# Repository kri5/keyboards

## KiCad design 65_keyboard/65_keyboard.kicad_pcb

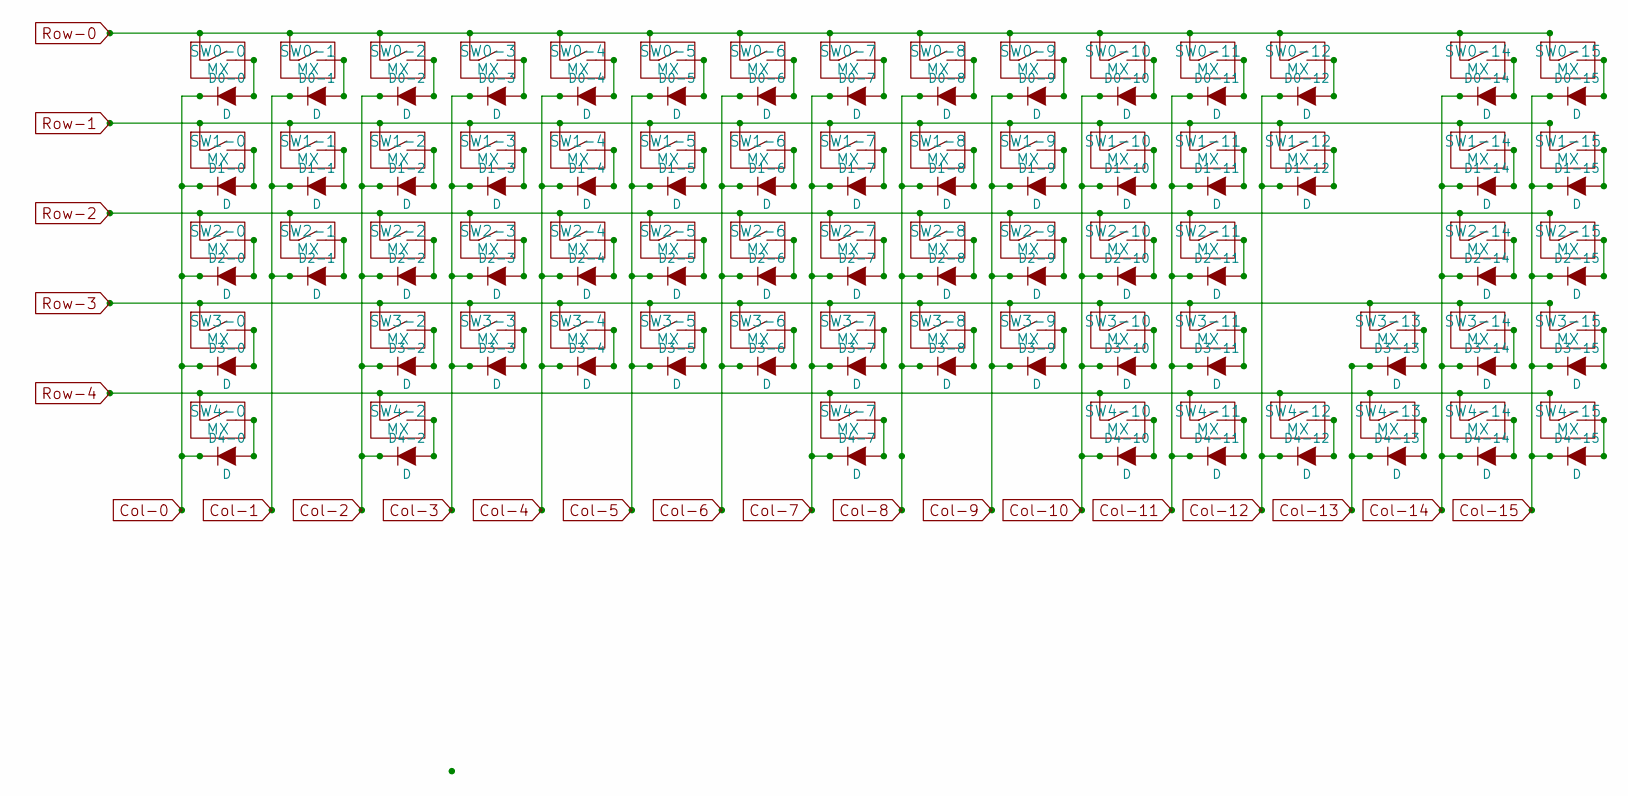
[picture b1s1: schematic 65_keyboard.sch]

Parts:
D0-0, D0-1, D0-2, D0-3, D0-4, D0-5, D0-6, D0-7, D0-8, D0-9, D0-10, D0-11, D0-12, D0-14, D0-15, D1-0, D1-1, D1-2, D1-3, D1-4, D1-5, D1-6, D1-7, D1-8, D1-9, D1-10, D1-11, D1-12, D1-14, D1-15, D2-0, D2-1, D2-2, D2-3, D2-4, D2-5, D2-6, D2-7, D2-8, D2-9, D2-10, D2-11, D2-14, D2-15, D3-0, D3-2, D3-3, D3-4, D3-5, D3-6, D3-7, D3-8, D3-9, D3-10, D3-11, D3-13, D3-14, D3-15, D4-0, D4-2, D4-7, D4-10, D4-11, D4-12, D4-13, D4-14, D4-15: D; Diode_DO-35_SOD27_Horizontal_RM10
SW0-0, SW0-1, SW0-2, SW0-3, SW0-4, SW0-5, SW0-6, SW0-7, SW0-8, SW0-9, SW0-10, SW0-11, SW0-12, SW0-15, SW1-1, SW1-2, SW1-3, SW1-4, SW1-5, SW1-6, SW1-7, SW1-8, SW1-9, SW1-10, SW1-11, SW1-12, SW1-15, SW2-1, SW2-2, SW2-3, SW2-4, SW2-5, SW2-6, SW2-7, SW2-8, SW2-9, SW2-10, SW2-11, SW2-15, SW3-2, SW3-3, SW3-4, SW3-5, SW3-6, SW3-7, SW3-8, SW3-9, SW3-10, SW3-11, SW3-14, SW3-15, SW4-11, SW4-13, SW4-14, SW4-15: MX; CHERRY_PLATE_100H
SW0-14: MX; CHERRY_PLATE_200H
SW1-0, SW1-14, SW4-2: MX; CHERRY_PLATE_150H
SW2-0, SW3-13, SW4-0: MX; CHERRY_PLATE_175H
SW2-14, SW3-0: MX; CHERRY_PLATE_225H
SW4-7: MX; CHERRY_PLATE_625H
SW4-10, SW4-12: MX; CHERRY_PLATE_125H

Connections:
Col-0: D0-0.1 (K), D1-0.1 (K), D2-0.1 (K), D3-0.1 (K), D4-0.1 (K)
Col-1: D0-1.1 (K), D1-1.1 (K), D2-1.1 (K)
Col-2: D0-2.1 (K), D1-2.1 (K), D2-2.1 (K), D3-2.1 (K), D4-2.1 (K)
Col-3: D0-3.1 (K), D1-3.1 (K), D2-3.1 (K), D3-3.1 (K)
Col-4: D0-4.1 (K), D1-4.1 (K), D2-4.1 (K), D3-4.1 (K)
Col-5: D0-5.1 (K), D1-5.1 (K), D2-5.1 (K), D3-5.1 (K)
Col-6: D0-6.1 (K), D1-6.1 (K), D2-6.1 (K), D3-6.1 (K)
Col-7: D0-7.1 (K), D1-7.1 (K), D2-7.1 (K), D3-7.1 (K), D4-7.1 (K)
Col-8: D0-8.1 (K), D1-8.1 (K), D2-8.1 (K), D3-8.1 (K)
Col-9: D0-9.1 (K), D1-9.1 (K), D2-9.1 (K), D3-9.1 (K)
Col-10: D0-10.1 (K), D1-10.1 (K), D2-10.1 (K), D3-10.1 (K), D4-10.1 (K)
Col-11: D0-11.1 (K), D1-11.1 (K), D2-11.1 (K), D3-11.1 (K), D4-11.1 (K)
Col-12: D0-12.1 (K), D1-12.1 (K), D4-12.1 (K)
Col-13: D3-13.1 (K), D4-13.1 (K)
Col-14: D0-14.1 (K), D1-14.1 (K), D2-14.1 (K), D3-14.1 (K), D4-14.1 (K)
Col-15: D0-15.1 (K), D1-15.1 (K), D2-15.1 (K), D3-15.1 (K), D4-15.1 (K)
unnamed: D0-0.2 (A), SW0-0.2 (B)
unnamed: D0-1.2 (A), SW0-1.2 (B)
unnamed: D0-2.2 (A), SW0-2.2 (B)
unnamed: D0-3.2 (A), SW0-3.2 (B)
unnamed: D0-4.2 (A), SW0-4.2 (B)
unnamed: D0-5.2 (A), SW0-5.2 (B)
unnamed: D0-6.2 (A), SW0-6.2 (B)
unnamed: D0-7.2 (A), SW0-7.2 (B)
unnamed: D0-8.2 (A), SW0-8.2 (B)
unnamed: D0-9.2 (A), SW0-9.2 (B)
unnamed: D0-10.2 (A), SW0-10.2 (B)
unnamed: D0-11.2 (A), SW0-11.2 (B)
unnamed: D0-12.2 (A), SW0-12.2 (B)
unnamed: D0-14.2 (A), SW0-14.2 (B)
unnamed: D0-15.2 (A), SW0-15.2 (B)
unnamed: D1-0.2 (A), SW1-0.2 (B)
unnamed: D1-1.2 (A), SW1-1.2 (B)
unnamed: D1-2.2 (A), SW1-2.2 (B)
unnamed: D1-3.2 (A), SW1-3.2 (B)
unnamed: D1-4.2 (A), SW1-4.2 (B)
unnamed: D1-5.2 (A), SW1-5.2 (B)
unnamed: D1-6.2 (A), SW1-6.2 (B)
unnamed: D1-7.2 (A), SW1-7.2 (B)
unnamed: D1-8.2 (A), SW1-8.2 (B)
unnamed: D1-9.2 (A), SW1-9.2 (B)
unnamed: D1-10.2 (A), SW1-10.2 (B)
unnamed: D1-11.2 (A), SW1-11.2 (B)
unnamed: D1-12.2 (A), SW1-12.2 (B)
unnamed: D1-14.2 (A), SW1-14.2 (B)
unnamed: D1-15.2 (A), SW1-15.2 (B)
unnamed: D2-0.2 (A), SW2-0.2 (B)
unnamed: D2-1.2 (A), SW2-1.2 (B)
unnamed: D2-2.2 (A), SW2-2.2 (B)
unnamed: D2-3.2 (A), SW2-3.2 (B)
unnamed: D2-4.2 (A), SW2-4.2 (B)
unnamed: D2-5.2 (A), SW2-5.2 (B)
unnamed: D2-6.2 (A), SW2-6.2 (B)
unnamed: D2-7.2 (A), SW2-7.2 (B)
unnamed: D2-8.2 (A), SW2-8.2 (B)
unnamed: D2-9.2 (A), SW2-9.2 (B)
unnamed: D2-10.2 (A), SW2-10.2 (B)
unnamed: D2-11.2 (A), SW2-11.2 (B)
unnamed: D2-14.2 (A), SW2-14.2 (B)
unnamed: D2-15.2 (A), SW2-15.2 (B)
unnamed: D3-0.2 (A), SW3-0.2 (B)
unnamed: D3-2.2 (A), SW3-2.2 (B)
unnamed: D3-3.2 (A), SW3-3.2 (B)
unnamed: D3-4.2 (A), SW3-4.2 (B)
unnamed: D3-5.2 (A), SW3-5.2 (B)
unnamed: D3-6.2 (A), SW3-6.2 (B)
unnamed: D3-7.2 (A), SW3-7.2 (B)
unnamed: D3-8.2 (A), SW3-8.2 (B)
unnamed: D3-9.2 (A), SW3-9.2 (B)
unnamed: D3-10.2 (A), SW3-10.2 (B)
unnamed: D3-11.2 (A), SW3-11.2 (B)
unnamed: D3-13.2 (A), SW3-13.2 (B)
unnamed: D3-14.2 (A), SW3-14.2 (B)
unnamed: D3-15.2 (A), SW3-15.2 (B)
unnamed: D4-0.2 (A), SW4-0.2 (B)
unnamed: D4-2.2 (A), SW4-2.2 (B)
unnamed: D4-7.2 (A), SW4-7.2 (B)
unnamed: D4-10.2 (A), SW4-10.2 (B)
unnamed: D4-11.2 (A), SW4-11.2 (B)
unnamed: D4-12.2 (A), SW4-12.2 (B)
unnamed: D4-13.2 (A), SW4-13.2 (B)
unnamed: D4-14.2 (A), SW4-14.2 (B)
unnamed: D4-15.2 (A), SW4-15.2 (B)
Row-0: SW0-0.1 (A), SW0-1.1 (A), SW0-2.1 (A), SW0-3.1 (A), SW0-4.1 (A), SW0-5.1 (A), SW0-6.1 (A), SW0-7.1 (A), SW0-8.1 (A), SW0-9.1 (A), SW0-10.1 (A), SW0-11.1 (A), SW0-12.1 (A), SW0-14.1 (A), SW0-15.1 (A)
Row-1: SW1-0.1 (A), SW1-1.1 (A), SW1-2.1 (A), SW1-3.1 (A), SW1-4.1 (A), SW1-5.1 (A), SW1-6.1 (A), SW1-7.1 (A), SW1-8.1 (A), SW1-9.1 (A), SW1-10.1 (A), SW1-11.1 (A), SW1-12.1 (A), SW1-14.1 (A), SW1-15.1 (A)
Row-2: SW2-0.1 (A), SW2-1.1 (A), SW2-2.1 (A), SW2-3.1 (A), SW2-4.1 (A), SW2-5.1 (A), SW2-6.1 (A), SW2-7.1 (A), SW2-8.1 (A), SW2-9.1 (A), SW2-10.1 (A), SW2-11.1 (A), SW2-14.1 (A), SW2-15.1 (A)
Row-3: SW3-0.1 (A), SW3-2.1 (A), SW3-3.1 (A), SW3-4.1 (A), SW3-5.1 (A), SW3-6.1 (A), SW3-7.1 (A), SW3-8.1 (A), SW3-9.1 (A), SW3-10.1 (A), SW3-11.1 (A), SW3-13.1 (A), SW3-14.1 (A), SW3-15.1 (A)
Row-4: SW4-0.1 (A), SW4-2.1 (A), SW4-7.1 (A), SW4-10.1 (A), SW4-11.1 (A), SW4-12.1 (A), SW4-13.1 (A), SW4-14.1 (A), SW4-15.1 (A)

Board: 2 copper layers, 134 parts (67 on the bottom side), 88 nets, no tracks yet.

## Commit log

2015-10-27 Adds third party libraries
2015-10-27 Adds first version of the project
2015-10-28 Adds all keys to keyboard, and places them on the PCB
2015-10-28 Removes useless junctions
